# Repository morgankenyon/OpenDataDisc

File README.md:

# OpenDataDisc

An open platform that allows disc golfers to collect their throw statistics.

> Your throw, your data, your platform.

## Pics

> Putter Dev Board

> Putter Board Mounted On Disc

I'm documentating my process over on my [youtube channel](https://www.youtube.com/@BlenderDiscGolf).

## Disc Golf + Analytics

I'd love the ablity to track and measure my disc golf throws without spending tons of money.

* Would it be easier to buy one of the currently available products? Probably.
* What's the likelihood this project never completes its goal? Higher than 0.

So why I am doing it? I'm a sucker for starting something new, I'm a software developer, have started playing disc golf and wanted a project to combine those 2.

Will that mix actually produce something usable? No idea.

## Current Project Phase

Phase: Putter version

As shown in the pics above, I have a putter dev board that I'm just starting to use to measure statistics of putts.

Putts are easier to measure due to low speeds and rpms.

## Project Phases (Somewhat flexible now)

* Getting to know hardware
  * Buying the hardware I think I need.
  * Hooking everything up.
  * Getting data flowing between microcontroller and computer.
  * Getting some basic calculations working
* Putter version (current phase)
  * Putts have slow RPMs and low Gs
    * These values are much easier to measure and test.
    * Hardware is also cheaper.
    * Will probably be using as many off the shelf parts as possible. (Nothing really custom designed)
  * Create a developer kit that can be used for putters.
    * Not something that would probably be widely available, but might create some dev kits for technical people wanting to help.
  * Need some hardware to confirm the sensor values.
    * Speed gun, high speed camera, etc
  * Most R&D on this project will be based on this platform.
* Alpha Driver Disc
  * To develop something to track high speed throws, will probably need:
    * Custom hardware
    * Beefed up software
    * More expensive testing equipment
* Beta Driver Disc
  * Create a more refined alpha setup
  * Any problems I encountered in the Alpha disc can be changed here
* Driver Disc
  * First proper product release
  * Should be easy for non technical people to setup and use
  * Lots of polish will need to happen before this is ready

## Repo Layout

This repo holds both [hardware](./hardware/README.md) and [software](./software/README.md) for the OpenDataDisc project. As this project is still in it's early phase, there's no instructions on how to build your own and run on your own computers. 

That information will come as the project progresses.

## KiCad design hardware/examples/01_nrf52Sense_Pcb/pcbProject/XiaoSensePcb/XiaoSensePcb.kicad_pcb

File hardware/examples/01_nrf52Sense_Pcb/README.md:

# NRF52 Sense PCB Design

After watching [this youtube video](https://www.youtube.com/watch?v=2vHB8AUQKWM), it made the point that if I am not planning on using Wifi, the esp32 is a bit overkill. I can reduce my power/battery requirements by picking another board.

So I landed on the NRF52 microcontroller. I specifically have bought a [Seeed Studio XIAO nRF52840 (Sense)](https://wiki.seeedstudio.com/XIAO_BLE/).

This experiment is an attempt to design a PCB that I can attach the dev board to, to one day put it on a disc.

Using a M3 mouting hole on the PCB. Based on Reddit below.

M3 screws have a Major Diameter of 3.0 mm, I made the mounting holes on my PCB 3.1 mm.

## Resources

* Mounting hole diameter - https://www.reddit.com/r/AskElectronics/comments/uet1u9/comment/i6qwwx0/?utm_source=share&utm_medium=web3x&utm_name=web3xcss&utm_term=1&utm_content=share_button
* Generating Gerber Files from Kica - https://www.pcbway.com/helpcenter/technical_support/Generate_Gerber_file_from_Kicad.html

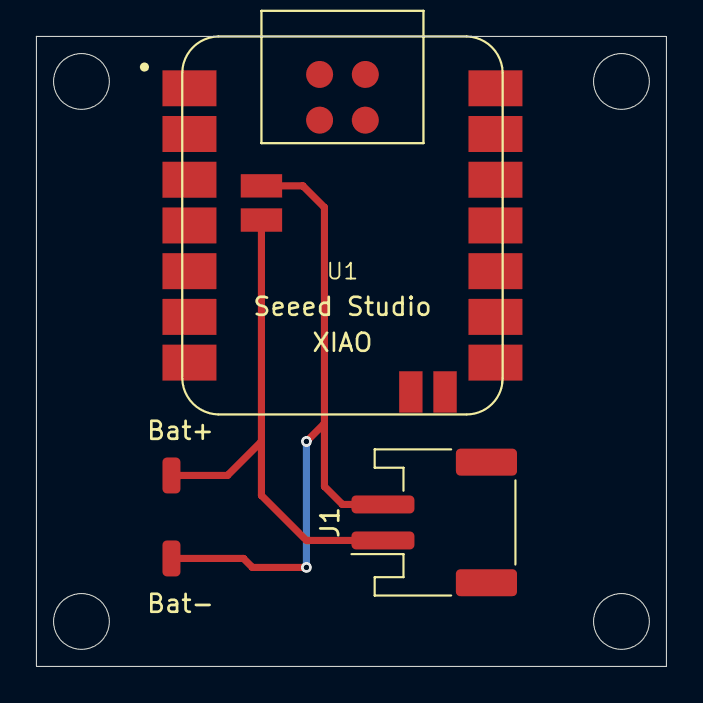
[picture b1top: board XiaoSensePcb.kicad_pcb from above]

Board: 2 copper layers, 35.0 x 35.0 mm, 4 parts (0 on the bottom side), 2 nets.

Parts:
Bat+: SolderWirePad_1x01_SMD_1x2mm
Bat-: SolderWirePad_1x01_SMD_1x2mm
J1: Conn_01x02; JST_PH_S2B-PH-SM4-TB_1x02-1MP_P2.00mm_Horizontal
U1: Seeed Studio XIAO nRF52840; XIAO-nRF52840-Sense-14P-2.54-21X17.8MM

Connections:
unnamed: Bat+.1, J1.1, U1.22 (BAT+)
unnamed: Bat-.1, J1.2, U1.21 (BAT-)

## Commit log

2024-05-18 Adding details around plan
2024-05-18 Updating language
2024-05-18 Adding hardware details
2024-05-18 Adding some more notes to the readme
2024-05-22 Changing licenses
2024-05-22 Adding first example to get bluetooth working
2024-05-23 Adding the 1st 3 example projects
2024-05-24 In progress work for bluetooth, something's not working
2024-05-25 Adding working code for esp to esp bluetooth connection
2024-05-25 Adding esp32 to esp32 bluetooth example, cleaning up the example
2024-05-25 Adding back server ino file, accidentally deleted it
2024-05-25 Adding file again
2024-05-25 Adding initial code and readme for esp32 to windows bluetooth connection
2024-05-26 Got notifications flowing from esp32 to windows, still work to do
2024-05-28 Rounding out readme for example 04
2024-05-28 Working on getting classic bluetooth working
2024-05-28 Example 05, getting blink working in platform IO
2024-05-28 Updating README to better clarify project phases
2024-05-28 Updating phase
2024-06-04 Adding example 6, using bluetooth through platformIO
2024-06-04 Cleaning up readme
2024-06-04 Adding script used to read bluetooth in example 6
2024-06-04 Laying groundwork for platformIO project to begin monitoring accelerometer readings
2024-06-05 Able to receive messages from esp32 in csharp
2024-06-06 Completing the csharp client
2024-06-06 Correcting saying
2024-06-06 correct use of disc
2024-06-06 Rename to example 8
2024-06-06 working 08 example before all the accelerometer code
2024-06-08 Working example of pushing accelerometer data to computer
2024-06-08 Cleaning up esp32 code
2024-06-08 Cleaning up readme for example 8
2024-06-12 Adding first 3d printed files examples
2024-06-24 Fixing small bug with disconnection
2024-06-25 Adding code to calibrate gyro
2024-06-25 Adding stuff for accelerometer angles
2024-06-25 Adding code for measuring angles using Accelerometer
2024-06-26 Adding a notes section
2024-06-26 Saving file
2024-06-26 Adding link to high performance sensors
2024-06-28 Adding links to schematics
2024-06-30 Adding notes from sensors
2024-07-01 Adding notes about hardware breakout board
2024-07-11 Adding hardware examples for nrf52Sense
2024-07-11 Adding a blink example for my nrf52 sense
2024-07-11 Adding example 12, accelerometer on the sense
2024-07-11 Adding screenshot of working code
2024-07-11 working on sense imu from platformio
2024-07-15 Updating code based on arduino example
2024-07-15 Adding platformIO example for builtin IMU
2024-07-15 Starting work in example 13
2024-07-15 Finishing up example 14
2024-07-16 Working on bluetooth connection for nrf52
2024-07-16 Cleaning up commented out code
2024-07-16 Getting byte array notify working
2024-07-16 Pushing string message to client
2024-07-16 Rolling back comments after fixing serial startup wait issue
2024-07-16 Updating README after some hardware changes to the project
2024-07-16 Updating README a bit
2024-07-17 Adding kicad files for xiao sense pcb board
2024-07-21 Adding last files for xiao sense pcb
2024-07-21 Adding some more info to the PCB design example
2024-07-21 Adding 02 putter housing
2024-07-22 Adding first Avalonian application, working through the sample tutorial
2024-07-24 Adding 3d design for putting housing
2024-07-24 Updating README
2024-07-26 Finishing Avalonia tutorial
2024-07-27 First attempt at example 17
2024-07-27 Adding bluetooth selector popup window
2024-07-31 Adding the ability to scan for bluetooth devices nearby
2024-08-03 Updating after completing bluetooth selector
2024-08-03 Removing the music store files from example 16
2024-08-03 Adding code to receive messages from the nrf52
2024-08-06 Adding the ability to display messages from bluetooth sensor on home page
2024-08-06 Updating the example readme
2024-08-07 Adding sqllite functionality in avalonia
2024-08-07 Forgot to save readme on example 18
2024-08-09 Rearranging project, promoting software out of examples folder
2024-08-09 Moving hardware snippet to the hardware readme
2024-08-09 In progress work trying to get ble characteristic to read more than 20 bytes
2024-08-26 Changing to sending accelerometer and gyro data at different times
2024-08-26 Exploring Avalonia's Grid.
2024-08-26 Changing main view of app over to grid view
2024-08-28 Adding the ability to create sqlite database to track data
2024-08-28 Removing unused file
2024-08-28 Adding developer documentation for project
2024-08-28 Adding some comments about future work
2024-08-28 Adding proper todos
2024-09-08 Adding project pictures
2024-09-08 Adding youtube channel link
2024-09-08 Keeping readme up to date
2024-09-08 Starting using channels to write sensor data to db
2024-09-09 Writing sensor data to database
2024-09-09 Moving sensor data to models namespace
2024-09-10 Starting work on having a loading display
2024-09-10 Using enum to track page state
2024-09-10 Adding a state to track bluetooth connection status
2024-09-10 Writing down error
2024-09-11 Writing the number of messages received
2024-09-11 Adding rate that messages are coming in
2024-09-11 Remove old comment
2024-09-11 Adding info on how full the channel is
2024-09-11 Removing delay from microcontroller
2024-09-16 Starting work on using the nrf Connect SDK
2024-09-17 Adding blink example for xiao sense board
2024-09-18 Adding .vscode to gitignore
2024-09-18 Adding two example projects
2024-09-19 Adding second blinky project while working through tutorial list
2024-09-20 Adding basic battery bluetooth service
2024-09-21 Adding code for the environmental sensing service
2024-09-21 Wrapping up bluetooth examples from wsn & iot
2024-09-21 Adding bluetooth example with notify permissions
2024-10-01 Adding some notes on the xiao sense imu
2024-10-01 Starting work on reading values from the IMU sensor
2024-10-01 Adding more code for temperature calculation
2024-10-02 Adding the ability to read from register and calculate temperature
2024-10-03 Correcting i2c device address
2024-10-04 Adding temperature sensing code, still need to clean it up
2024-10-05 Cleaning up code, updating memory address logic
2024-10-05 Adding example 24
2024-10-05 Adding the start of configuring the IMU sensor
2024-10-06 Rounding out the accelerometer configuration for CTRL1_XL register
2024-10-06 Adding gyro configuration
2024-10-06 First time reading accelometer sensor data
2024-10-06 Working on getting all accelerometer values, still got some debugging to do
2024-10-06 Correcting which buffer is being read from.
2024-10-07 Fixing the accelerometer scaling problem
2024-10-07 Adding calculation for gyro values
2024-10-07 Adding final code changes to this example, printing out both acc and gyro data
2024-10-08 Renaming struct names
2024-10-08 Finishes combination call
2024-10-08 Adding new project for Zephyr + BLE
2024-10-08 Starting to add BLE service information
2024-10-09 Upping bluetooth message size, pushing accelerometer values over bluetooth
2024-10-09 Sending gyro data across bluetooth as well
2024-10-10 Fixing client to save all 6 data points at once
2024-10-10 Updating example readme
2024-10-10 Starting the bulk bluetooth project
2024-10-15 Sending timestamp over the bluetooth message
2024-10-16 Moving microcontroller code from platformIO to zephyr
2024-10-16 Removing unused code
2024-10-16 Removing old code
2024-10-17 Adding the ability to disconnect from a bluetooth device
2024-10-17 Allowing token to be cancelled if device disconnects, still some bugs
2024-10-18 Fixing reconnecting to bluetooth device after device loses power
2024-10-18 Only pushing bluetooth messages when there's a bluetooth connection
2024-10-18 Removing commented out code
2024-10-23 Trying to write to bluetooth device
2024-10-23 Fixing the write response issue
2024-10-24 In progress work trying to get the UI configuration setup working
2024-10-27 Making configuration part of the bluetooth listening process
2024-10-27 Continued changes to get configuration working
2024-10-28 Piping messages to the configuration window
2024-10-28 Extracting out receiving sensor readings
2024-10-28 Displaying sensor data in configuration
2024-10-28 Adding the ability to move steps in configuration
2024-10-28 Continuing work on configuration dialog
2024-10-29 Getting logic for configuration modal working, still need saving and styling a bit
2024-10-31 Working on getting configuration data saved
2024-10-31 Repositioning the configuration panel
2024-10-31 Hiding configuring value when it's not needed
2024-10-31 Removing unneeded code
2024-10-31 Fixing whitespace difference
2024-10-31 Removing unneeded comment
2024-10-31 Getting ScottPlot demo working
2024-10-31 Adding streaming plot example
2024-11-01 Changing up data source of scroll plot
2024-11-01 Graphing 2 dimensions of sensor data
2024-11-02 Attempting to implement an extended kalman filter
2024-11-05 Working on getting another extended kalman filter working
2024-11-05 In progress work
2024-11-05 Still working on Kalman filter
2024-11-05 Further debugging of kalman filter
2024-11-07 Continued work on Kalman filter
2024-11-08 Fixing some bugs with Kalman filter, still more work to do
2024-11-09 Continuing to tweak with the kalman filter
2024-11-15 Adding config values
2024-11-15 Adding new config values, setting up test Kalman filter project
2024-11-15 In progress work on kalman filter
2024-11-15 Prepping sample data
2024-11-16 Graphing real data
2024-11-16 In progress work on getting the kalman filter working
2024-11-19 In progress workin trying ot understand Kalman filters
2024-11-20 Adding recap of GH Filter
2024-11-21 Adding notes when going through Kalman filter course
2024-11-27 Updating notes for Kalman filter
2024-11-28 Adding more notes
2024-12-07 Adding C# code for walking through the GH filter works
2024-12-07 Continuing to work on gh filter section and code
2024-12-08 Continuing C# work to copy Python Kalman filter code
